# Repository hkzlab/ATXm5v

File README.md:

# ATX -5V inline injector

## Introduction

I needed a quick and cheap way to get -5V available on a modern ATX PSU. The current requirements were risible, so I just made an inline module that takes -12V and regulates down to -5V using a simple and cheap 7905.

### Disclaimer

I take NO responsibility for what happens if you decide to build and use this device. Your computer might crash, catch fire or be destroyed in other nasty ways.

## Bill of Materials

| Component         | Qty | Type / Value          |
| ----------------- | --- | --------------------- |
| J1                |  1  | Molex 39-30-1200      |
| J2                |  1  | Molex 172708-0020     |
| Pins for J2       |  20 | Molex 172718-1111     |
| U1                |  1  | 7905 (TO-263)         |
| C1                |  1  | 10uF/16v 1206 ceramic |
| C2                |  1  | 100nF 1206 ceramic    |

### Notes

Cut away the excess plastic from the Molex 172708-0020, fit in all the pins, and then slide the PCB between them. Then solder them, making sure they don't touch.

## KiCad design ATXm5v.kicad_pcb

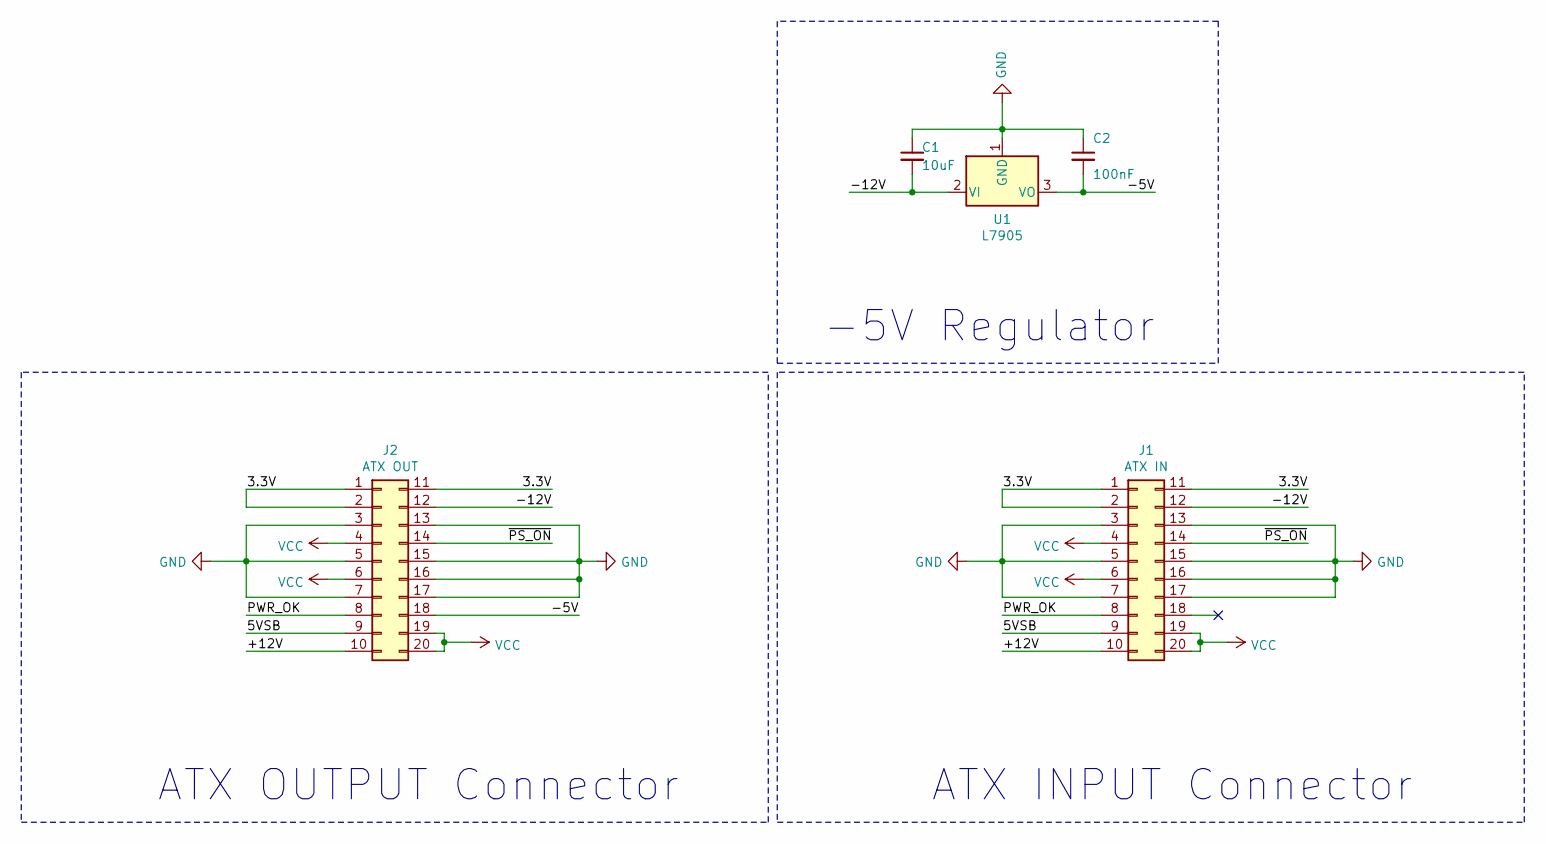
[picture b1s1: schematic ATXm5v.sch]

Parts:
C1: 10uF; C_1206_3216Metric_Pad1.33x1.80mm_HandSolder
C2: 100nF; C_1206_3216Metric_Pad1.33x1.80mm_HandSolder
J1: ATX IN; Molex_Mini-Fit_Jr_5569-20A2_2x10_P4.20mm_Horizontal
J2: ATX OUT; ATX-Edge
U1: L7905; TO-263-3_TabPin2

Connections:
/3.3V: J1.1, J1.2, J1.11, J2.1, J2.2, J2.11
/5VSB: J1.9, J2.9
/+12V: J1.10, J2.10
/-5V: C2.2, J2.18, U1.3 (VO)
/-12V: C1.2, J1.12, J2.12, U1.2 (VI)
/PWR_OK: J1.8, J2.8
/~PS_ON: J1.14, J2.14
GND: C1.1, C2.1, J1.3, J1.5, J1.7, J1.13, J1.15, J1.16, J1.17, J2.3, J2.5, J2.7, J2.13, J2.15, J2.16, J2.17, U1.1 (GND)
VCC: J1.4, J1.6, J1.19, J1.20, J2.4, J2.6, J2.19, J2.20

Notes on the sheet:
-5V Regulator
ATX INPUT Connector
ATX OUTPUT Connector

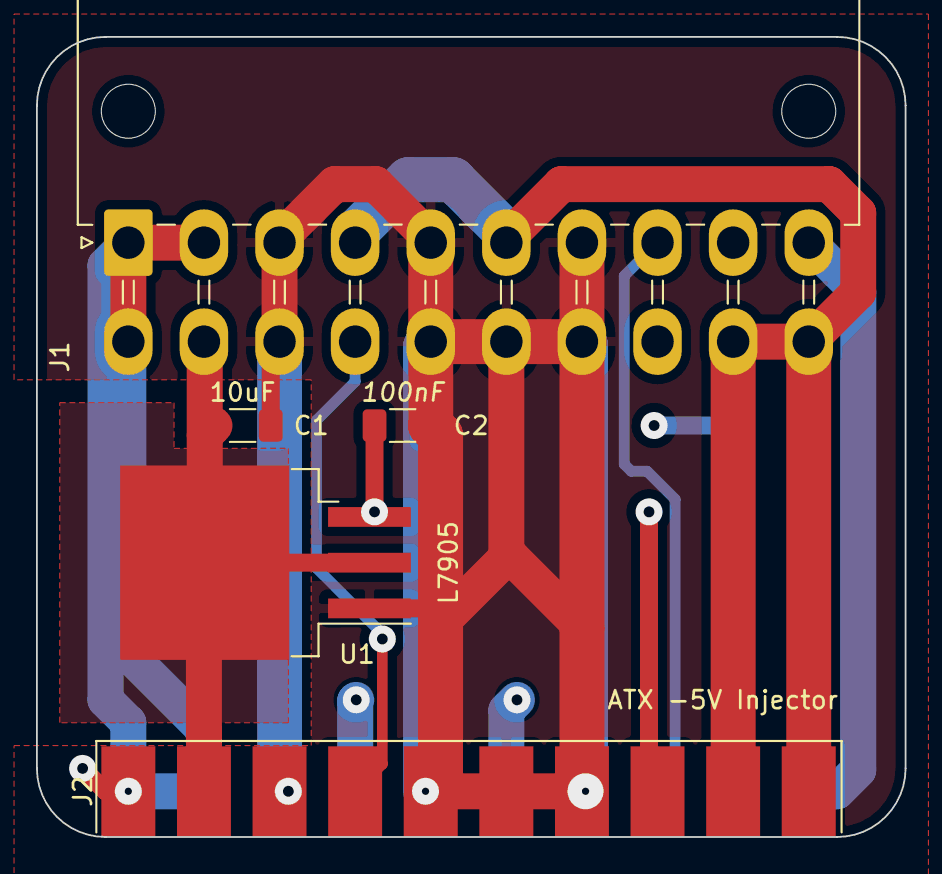
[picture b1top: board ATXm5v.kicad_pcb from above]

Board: 4 copper layers, 48.3 x 44.5 mm, 5 parts (0 on the bottom side), 9 nets.

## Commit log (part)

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2021-09-25 Add initial pcb
2021-09-25 Add heatsink plane for regulator
2021-09-25 Add relief for linear reg
2021-09-25 First revision of the board
2021-09-29 basic gerbers
2021-09-29 Fix footprint
2021-10-02 Fixed connector direction
2021-10-25 Add README and pics
2021-10-25 Update image
2021-11-09 Change KiCad URL
